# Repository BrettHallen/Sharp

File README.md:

# Sharp Projects
Projects for Sharp computers.<br>

So far:
- Sharp MZ-80B
- Sharp PC-1350
- Sharp PC-2500

## [Sharp MZ-80B](/Sharp_MZ-80B)
Currently still under its own repository but I'll move it here at some stage.

## [Sharp PC-1350](/Sharp_PC-1350)
The Sharp PC-1350 is the smaller sibling of the PC-2500.  It has the same screen resolution and BASIC but doesn't have the built-in phone book and business programs ... nor the plotter and cassette interface (these require a dock like the CE-125).

## [Sharp PC-2500](/Sharp_PC-2500)
The Sharp PC-2500 (export) and PC-2500S (domestic Japanese) were a development of the PC-1350 Pocket Computer in an A4-form factor with a full-size QWERTY keyboard and built-in 4-colour/pen plotter/printer.

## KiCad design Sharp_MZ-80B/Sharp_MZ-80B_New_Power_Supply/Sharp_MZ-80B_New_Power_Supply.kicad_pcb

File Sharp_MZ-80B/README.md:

# Sharp MZ-80B
My little repository of information about Sharp's MZ-80B all-in-one business computer from 1981.<br>

The MZ-80B is an evolution of the MZ-80K.<br>

WORK IN PROGRESS.<br>

NOTE! Any PCB designs are untested unless stated otherwise.  I have done my best to recreate them based on the schematics in the Service Manual.  (15/Feb/2026)<br>

## Videos
- [Part 1: Initial look & disassembly](https://youtu.be/cHQdRs1u79s)
- [Part 2: Keyboard refurbishment starts](https://youtu.be/vS2Di7rVlAI)
- [Part 3: Power Supply](https://youtu.be/JZkt_DzX6Ko)
- [Part 4: Monitor & Tape Deck](https://youtu.be/Ke3hOiWCVKM)
- [Part 5: New power supply](https://youtu.be/C5JBbC6FNag)
- [Part 6: It kinda works](https://youtu.be/guZFLZZtFYg)

## Specs
- Z80 at 4MHz (LH0080A)
- Power: ±5V, +12V
- 32KB RAM, expandable to 64KB
- 2KB ROM (Initial Program Loader, IPL)
- 2KB Character Generator ROM
- 2KB Character RAM
- 8KB Graphics RAM, expandable to 16KB (MZ-80GMK)

## [Components](/Sharp_MZ-80B/Components)
- IC2: Sharp X0240PA (Gate Array 14297)
- IC3: Sharp LH0080A (Z80 CPU)
- IC8: Sharp IX0285PA (IPL Boot ROM, 334-5700)
- IC19: 8253 PIT (Progammable Interval Timer)
- IC23: NEC D8255AC-5 PPI (Programmable Peripheral Interface)
- IC24: Sharp LH0081A (Z80 PIO)
- IC41: Toshiba TMM2016P-1 (2KB S-RAM)
- IC42: Sharp X0241PA (Gate Array 14298)
- IC43: Sharp X0242PA (Gate Array 14299)
- IC44: Sharp IX0286PA (CG-ROM, 334P-5701)
- DRAM: Sharp LH4116-3 (16k x 1-bit)

## [Manuals](/Sharp_MZ-80B/Manuals)
- MZ-80B Service Manual
- MZ-80B Owners Manual
- MZ-80 Monitor Reference Manual (SB-1520)

## [ROMs](/Sharp_MZ-80B/ROMs)
- 2KB Initial Program Loader (IPL)
- 2KB Character Generator
- 2KB RAM CHECK re-creation (needs testing)

## [32KB RAM Expansion](/Sharp_MZ-80B/Sharp_MZ-80B_RAM_III_IV_Expansion)
Internal expansion board to increase the RAM from 32KB to 64KB.  This design is from the Service Manual and so currently uses 4116 RAM chips.<br>

## [Base 8KB Graphics RAM (MZ-80GM)](/Sharp_MZ-80B/Sharp_MZ-80GM)
Reproduction of the base graphics RAM card (a.k.a. "GRAPHYICS-1") in the Sharp MZ-80B based on the service manual schematics.  I've updated it by replacing the original four 2KB 2016 SRAM chips with a single 32KB 62256.  Overkill, yes, but the 62256 is still available new - it reduces the chip count by four.<br>

## [8KB Graphics RAM Expansion (MZ-80GMK)](/Sharp_MZ-80B/Sharp_MZ-80GMK)
Expansion board (a.k.a. "GRAPHYICS-2") that connects to the internal Expansion Port (MZ-80EU) that doubles the graphics video RAM from 8KB to 16KB.  This design is from the Service Manual but uses a 32KB 62256 as these are still available new, rather than an obsolete 8KB 6264 or four 2KB 2016.<br>

## [DRAM to SRAM](/Sharp_MZ-80B/Sharp_MZ-80B_DRAM-to-SRAM)
Idea to replace the 16 x 4116 DRAMs of the original 32KB RAM plus the additional 16 x 4116 DRAMs of the expansion RAM with two 62256 SRAMs.<br>

## [Keyboard](/Sharp_MZ-80B/Keyboard)
Schematic and replacement PCB design.<br>

## [SD Card Interface](https://github.com/yanataka60/MZ-2000_SD)
Design (not mine!) to add SD card interface for the MZ-80B (and others).  It will work in an 80B with or without the Expansion Unit installed, which is neat.

## [Combo Graphics RAM + SD Interface](/Sharp_MZ-80B/Sharp_MZ-80GMSD)
As my MZ-80B doesn't have an expansion unit I thought about trying to add the 8KB Graphics RAM expansion (MZ-80GMK) aka "GRAPHYCS-2" on the same board as the SD interface above.  The SD board itself is still external, but the connection to the MZ-80B motherboard is included with the graphics RAM expansion.

## Power 
My 80B came from Japan so expects 100VAC and not the 240VAC we use in Australia.

### DC Requirements
| Voltage          | Current | Use                                |
|------------------|---------|------------------------------------|
| +5V regulated    | 2.5A    | motherboard & tape deck            |
| -5V regulated    | 10mA    | DRAM                               |
| +12V regulated   | 1.25A   | monitor & tape deck                |
| +12V unregulated |         | 9.5V-16.5V for tape deck solenoids |

### Connectors
Thanks to [Brad](https://www.youtube.com/@zbradbell) for figuring out they are TJC1-type.<br>

| Sharp ID      | TJC Type     | Use                                         |
|---------------|--------------|---------------------------------------------|
| QPLGN0303CEZZ | TJC1-3A      | 3-pin terminal for tape deck power on PSU   |
| DSOCN0083PAZZ | TJC1-3Y      | 3-pin socket & wires from tape deck to PSU  |
| QPLGN0103CEZZ | TJC1-1A      | 1-pin terminal for monitor power on PSU     |
| DSOCN0083PAZZ | TJC1-1Y      | 1-pin socket & wire from monitor to PSU     |
| DSOCN0098PAZZ | TJC1-4Y      | 4-pin socket & wire from PSU to motherboard |
| QPLGN0403CEZZ | TJC1-4A      | 4-pin terminal on motherboard               |
| QPLGN0303CEZZ | TJC1-3A      | 3-pin terminal for Expansion Unit power     |
|               | TJC1-T       | Contact type for sockets                    |

- [QPLGN0303CEZZ](/Sharp_MZ-80B/Images/Sharp_MZ-80B_QPLGN0303CEZZ_1.jpg)
- [DSOCN0098PAZZ](/Sharp_MZ-80B/Images/Sharp_MZ-80B_DSOCN0098PAZZ_1.png)

### New DC Power Supply
To solve my 240VAC-to-100VAC problem I thought about using a DC power supply input and then lazily using modern DC-DC switching regulators.  The main issue I can see is that the original design uses an unregulated +12VDC to power the tape eject solenoid.  This is picked up from the rectified transformer output before the +12VDC regulator which powers the monitor & tape.<br>

The tape solenoid expects a voltage between 9.5V and 16.5V.<br>

My idea was to, ahem, simply use a +15VDC input for the solenoid, and then use separate +5V, -5V and +12V regulators for the regulated supplies.  I've added some capacitors to try to soak up any voltage spikes generated by the solenoid action.<br>

Some notes:
- If I can replace the DRAM with SRAM, there is no longer a need for the -5V rail
- If I don't physically use the tape deck then there is no need for the +15V, i.e. "unregulated +12V"

## [External Audio/Video Output](/Sharp_MZ-80B/Sharp_MZ-CVBS)
A re-design of an [existing design](https://github.com/gamo256/MZ_CVBS) for replacing the CRT with an LCD, I think.  The original design uses obsolete parts (well, hard to get in Australia) so I've tried to re-design.  Let's see if it works ...<br>

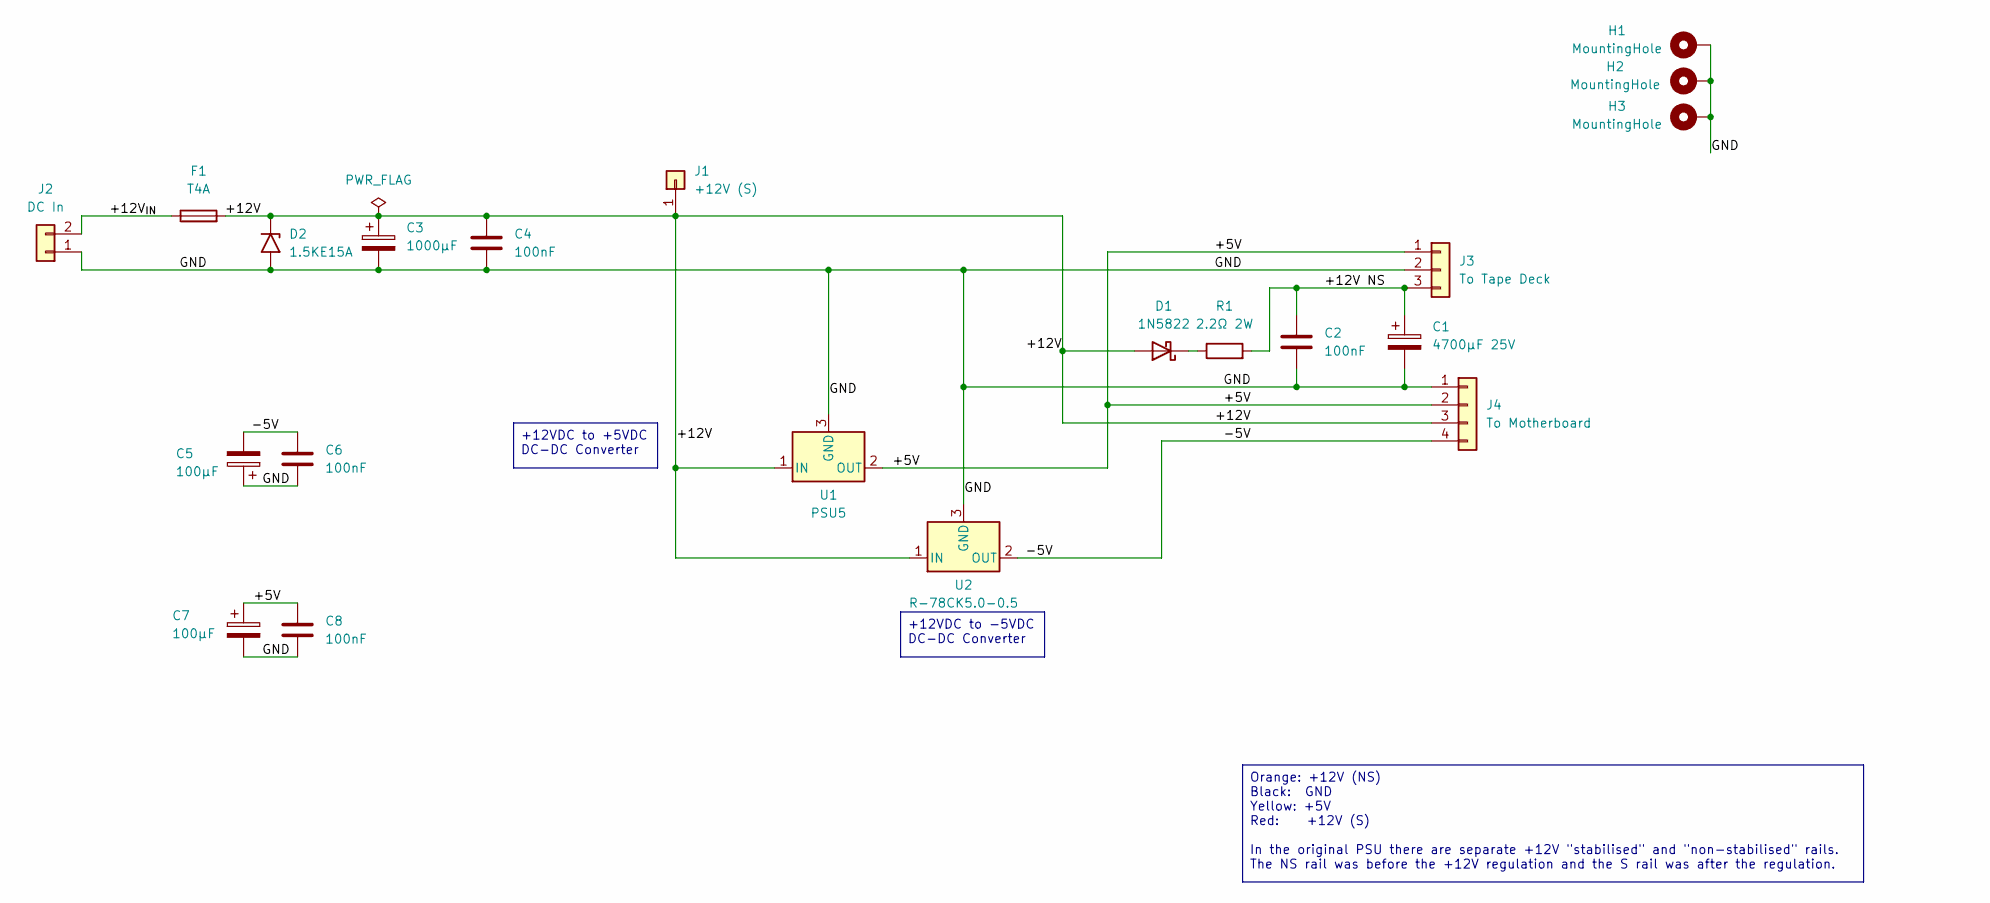
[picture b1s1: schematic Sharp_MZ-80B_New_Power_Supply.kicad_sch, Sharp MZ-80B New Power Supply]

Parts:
C1: 4700µF 25V; CP_Axial_L40.0mm_D16.0mm_P48.00mm_Horizontal
C2, C4, C6, C8: 100nF; C_Disc_D4.7mm_W2.5mm_P5.00mm
C3: 1000µF; CP_Radial_D16.0mm_P7.50mm
C5, C7: 100µF; CP_Radial_D7.5mm_P2.50mm
D1: 1N5822; D_DO-201AD_P15.24mm_Horizontal
D2: 1.5KE15A; D_DO-201AE_P15.24mm_Horizontal
F1: T4A; Littelfuse_5x20mm
H1, H2, H3: MountingHole; MountingHole_3.2mm_M3_DIN965_Pad_TopBottom
J1: +12V (S); TJC1-1A
J2: DC In; TJC1-2A
J3: To Tape Deck; TJC1-3A
J4: To Motherboard; TJC1-4A
R1: 2.2Ω 2W; R_Axial_DIN0414_L11.9mm_D4.5mm_P15.24mm_Horizontal
U1: PSU5; TO-3
U2: R-78CK5.0-0.5; TO-220-3_Vertical

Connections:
/+5V: C7.1, C8.1, J3.1, J4.2, U1.2 (OUT)
/+12V: C3.1, C4.1, D1.2 (A), D2.1 (A1), F1.2, J1.1 (Pin_1_1), J4.3, U1.1 (IN), U2.1 (IN)
/+12V NS: C1.1, C2.1, J3.3, R1.2
/+12V_{IN}: F1.1, J2.2
/-5V: C5.2, C6.1, J4.4, U2.2 (OUT)
/GND: C1.2, C2.2, C3.2, C4.2, C5.1, C6.2, C7.2, C8.2, D2.2 (A2), H1.1 (1_1), H2.1 (1_1), H3.1 (1_1), J2.1, J3.2, J4.1, U1.3 (GND), U2.3 (GND)
unnamed: D1.1 (K), R1.1

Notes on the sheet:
+12VDC to +5VDC DC-DC Converter
+12VDC to -5VDC DC-DC Converter
Orange: +12V (NS) Black: GND Yellow: +5V Red: +12V (S) In the original PSU there are separate +12V "stabilised" and "non-stabilised" rails. The NS rail was before the +12V regulation and the S rail was after the regulation.

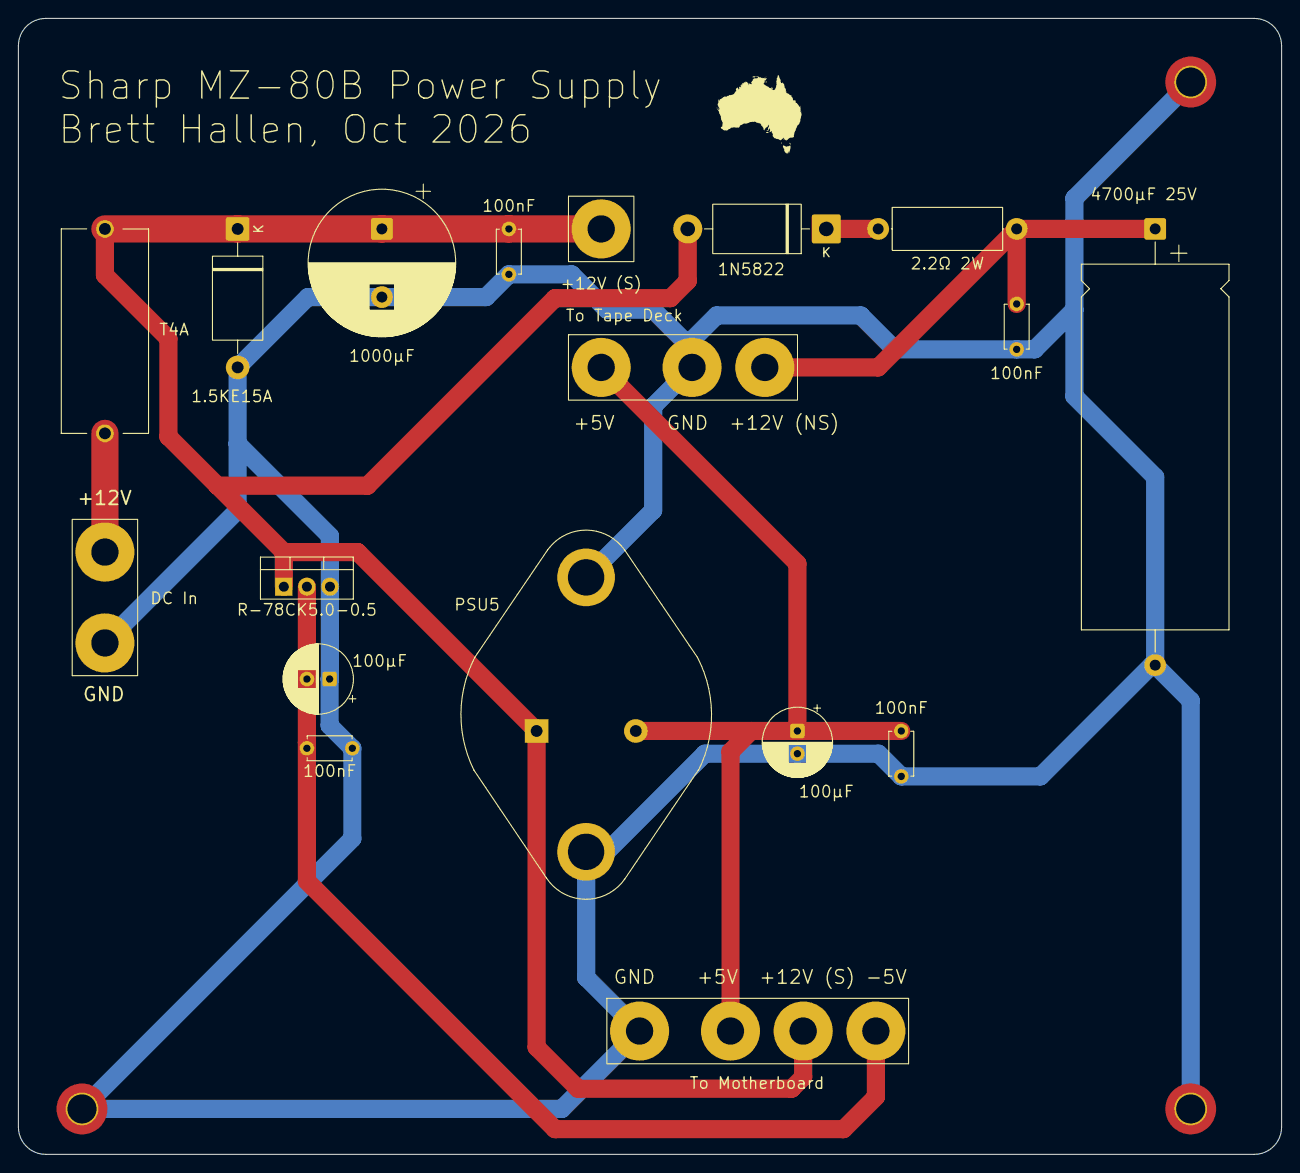
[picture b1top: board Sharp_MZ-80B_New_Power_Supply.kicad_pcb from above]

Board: 2 copper layers, 139.0 x 125.0 mm, 21 parts (0 on the bottom side), 7 nets.

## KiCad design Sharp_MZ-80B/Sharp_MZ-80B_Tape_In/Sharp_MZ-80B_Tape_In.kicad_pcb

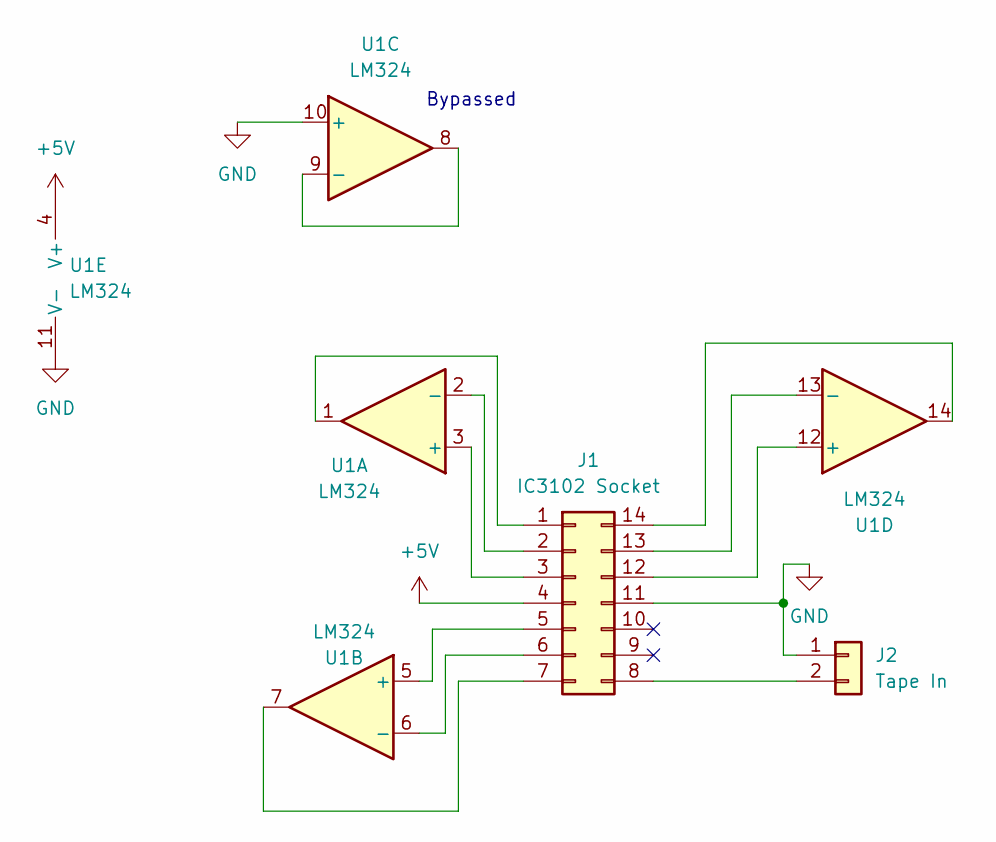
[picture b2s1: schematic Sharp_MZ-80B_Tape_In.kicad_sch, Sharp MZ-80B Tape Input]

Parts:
J1: IC3102 Socket; DIP-14_W7.62mm
J2: Tape In; PinHeader_1x02_P2.54mm_Vertical
U1: LM324; DIP-14_W7.62mm

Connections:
+5V: J1.4, U1.4 (V+)
GND: J1.11, J2.1, U1.10 (+), U1.11 (V-)
unnamed: J1.1, U1.1
unnamed: J1.2, U1.2 (-)
unnamed: J1.3, U1.3 (+)
unnamed: J1.5, U1.5 (+)
unnamed: J1.6, U1.6 (-)
unnamed: J1.7, U1.7
unnamed: J1.8, J2.2
unnamed: J1.12, U1.12 (+)
unnamed: J1.13, U1.13 (-)
unnamed: J1.14, U1.14
unnamed: U1.8, U1.9 (-)

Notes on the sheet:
Bypassed

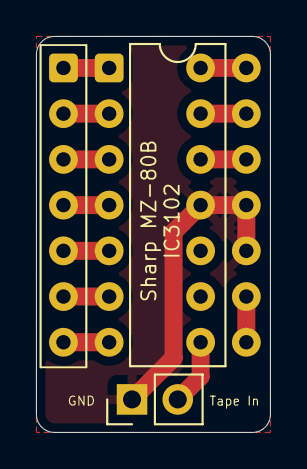
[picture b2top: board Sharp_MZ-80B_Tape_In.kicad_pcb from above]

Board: 2 copper layers, 13.0 x 22.0 mm, 3 parts (0 on the bottom side), 13 nets.

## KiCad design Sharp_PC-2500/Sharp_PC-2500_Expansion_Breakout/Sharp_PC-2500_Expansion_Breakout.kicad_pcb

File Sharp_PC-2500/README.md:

# Sharp PC-2500
The Sharp PC-2500 was a development of the Sharp PC-1350.  There were two models:<br>
- PC-2500 (export version)
- PC-2500S (domestic Japanese version)

It's an A4 format Portable Computer ... or Electronic Calculator depending on which side of the case you look at ... that runs S-BASIC and has built-in business applications.  <br>

Its 150x32 pixel LCD is capable of 24x4 characters.<br>

It uses an Hitachi SC61860 8-bit CPU with an internal 8KB ROM (code A14) for BIOS.  The S-BASIC and business applications are provided on an additional two 32KB ROMs giving 72KB of ROM in total.<br>

The other main chips are:
- SC61J216F (gate array)
- DLG3001E (PCU, printer control unit)
- SC43537 (DISP1 to DISP5)
- SC613256 (ROM1 & ROM2)
- HM6116LFP (RAM5 & RAM6)

The ROM1 code is FS43 for both models - this is S-BASIC.<br>
The ROM2 code is FS44 for Japan domestic and FS45 for export - this is for the business applications.<br>

It's quoted as having 5KB of RAM built-in but this seems inflated seeing as it only has a pair of 2KB RAM chips ... perhaps they are including the screen RAM?  The RAM can be expanded with either an 8KB or 16KB battery-backed RAM card.<br>

It includes a four pen/colour plotter/printer and has cassette and serial I/O ports.<br>

## [Manuals](/Sharp_PC-2500/Manuals)
Service manual for the PC-1350 and PC-2500.  The PC-1350 is included as it has the schematic for the CE-201 & CE-202 RAM cards.

## Videos
- [Part 1: First Look & Starting Repairs](https://youtu.be/iG-5hE-S3hM)
- [Part 2: RAM Card & Further Repairs](https://youtu.be/53tDbK7_jwQ)
- [Part 3: A working machine!](https://youtu.be/MAOv5fjzpVc)
- [Part 4: SKI JUMP Game](https://youtu.be/hhp-MKJ1q-c)

## [Internal RAM Upgrade](/Sharp_PC-2500/Sharp_PC-2500_RAM_Upgrade)
My idea to replace the RAM card interface PCB with a 16KB RAM upgrade to permanently give the machine 20KB of RAM.

## [Expansion Breakout Board](/Sharp_PC-2500/Sharp_PC-2500_Expansion_Breakout)
A breakout board for the RAM CARD interface.<br>

## [Programmes](/Sharp_PC-2500/Programmes)
I'm not aware of any programs available for this computer apart from CommAid.  The manual does have a section on how to convert programs for the PC-1210, PC-1245, PC-1260, PC-1350 and PC-1401.<br>

- Ski Jump (from the manual)

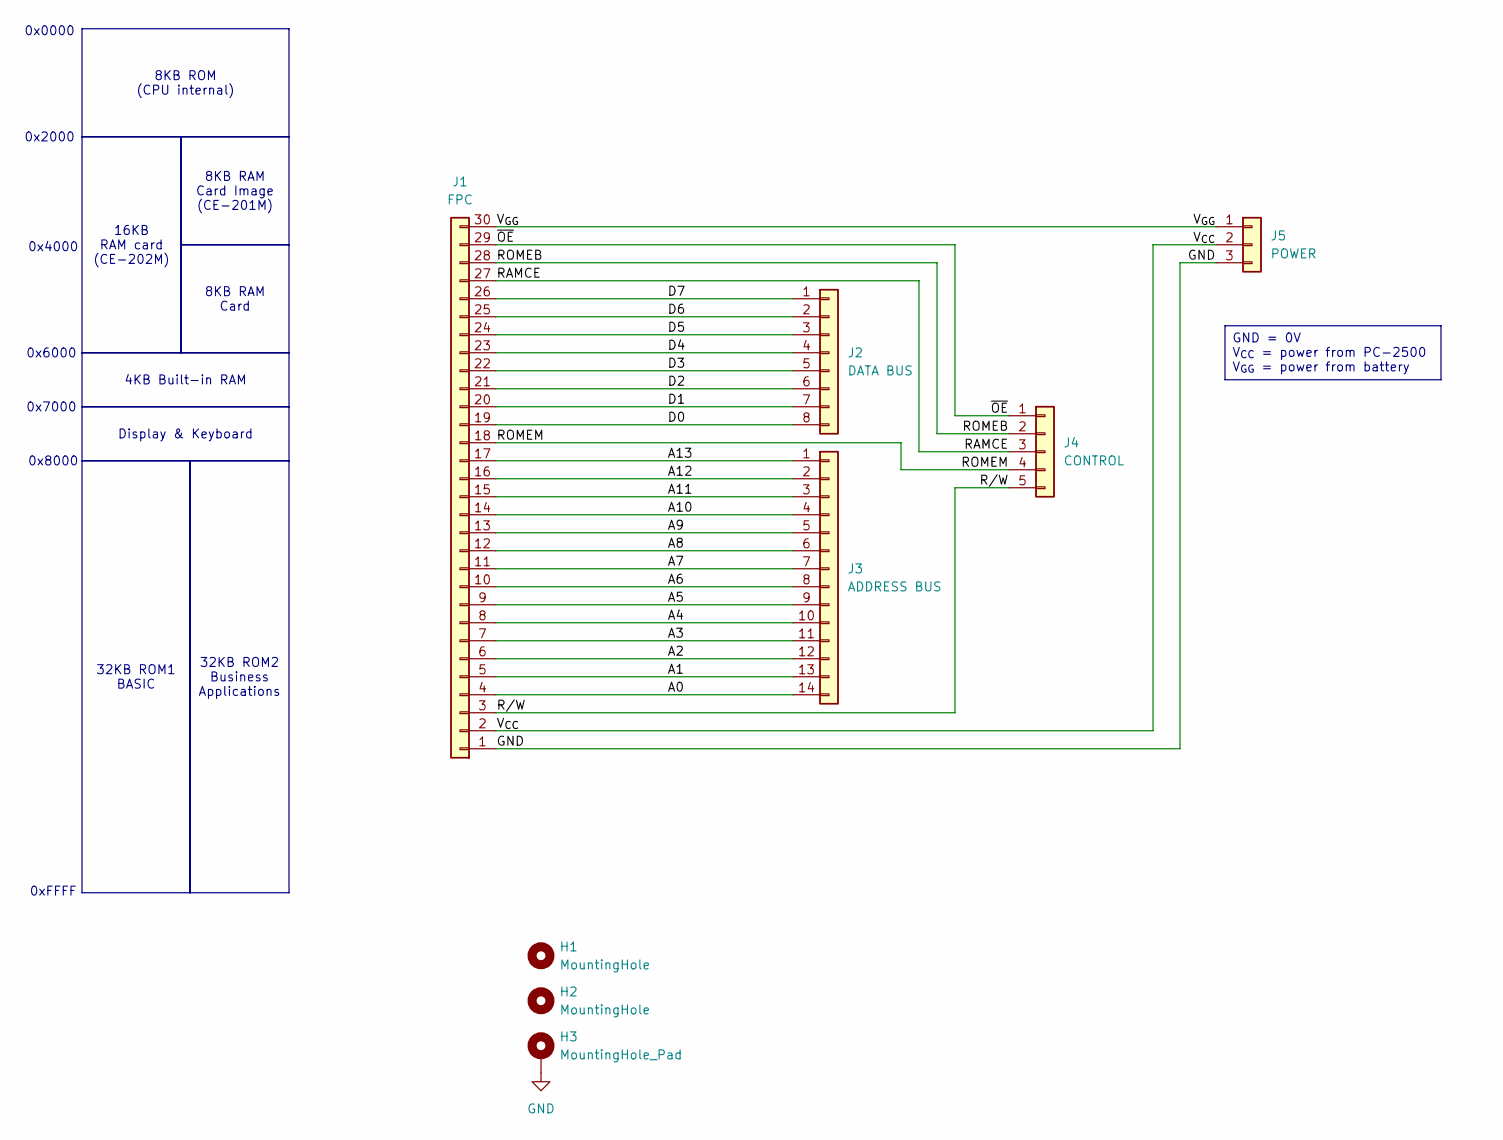
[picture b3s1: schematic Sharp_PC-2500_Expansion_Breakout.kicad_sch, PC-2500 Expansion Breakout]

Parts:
H1, H2: MountingHole; MountingHole_3.2mm_M3
H3: MountingHole_Pad; MountingHole_3.2mm_M3_DIN965_Pad_TopBottom
J1: FPC; Sharp PC-2500 30-pin TFC Connector
J2: DATA BUS; PinHeader_1x08_P2.54mm_Horizontal
J3: ADDRESS BUS; PinHeader_1x14_P2.54mm_Horizontal
J4: CONTROL; PinHeader_1x05_P2.54mm_Horizontal
J5: POWER; PinHeader_1x03_P2.54mm_Horizontal

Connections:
/A0: J1.4, J3.14
/A1: J1.5, J3.13
/A2: J1.6, J3.12
/A3: J1.7, J3.11
/A4: J1.8, J3.10
/A5: J1.9, J3.9
/A6: J1.10, J3.8
/A7: J1.11, J3.7
/A8: J1.12, J3.6
/A9: J1.13, J3.5
/A10: J1.14, J3.4
/A11: J1.15, J3.3
/A12: J1.16, J3.2
/A13: J1.17, J3.1
/D0: J1.19, J2.8
/D1: J1.20, J2.7
/D2: J1.21, J2.6
/D3: J1.22, J2.5
/D4: J1.23, J2.4
/D5: J1.24, J2.3
/D6: J1.25, J2.2
/D7: J1.26, J2.1
/RAMCE: J1.27, J4.3
/ROMEB: J1.28, J4.2
/ROMEM: J1.18, J4.4
/R/W: J1.3, J4.5
/V_{CC}: J1.2, J5.2
/V_{GG}: J1.30, J5.1
/~OE: J1.29, J4.1
GND: H3.1 (1_1), J1.1, J5.3

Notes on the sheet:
0x7000
0x8000
0x4000
0x2000
0xFFFF
0x6000
0x0000
32KB ROM2 Business Applications
Display & Keyboard
8KB RAM Card Image (CE-201M)
32KB ROM1 BASIC
16KB RAM card (CE-202M)
8KB RAM Card
8KB ROM (CPU internal)
4KB Built-in RAM
GND = 0V V_{CC} = power from PC-2500 V_{GG} = power from battery

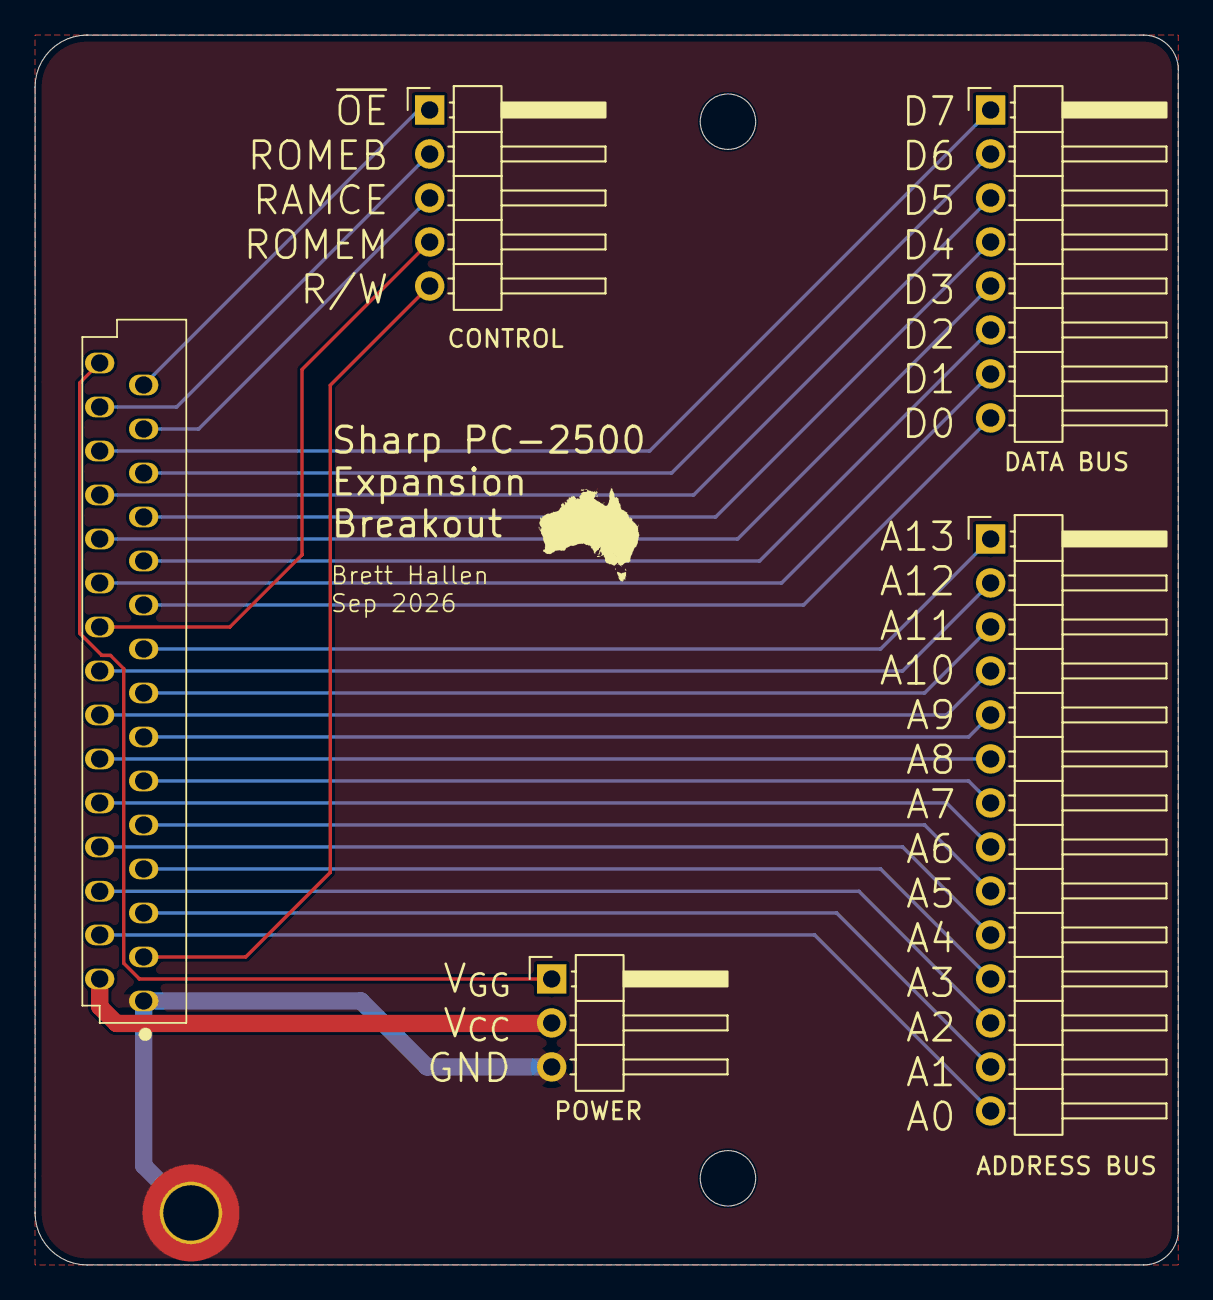
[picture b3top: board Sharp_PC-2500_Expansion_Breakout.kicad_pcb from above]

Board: 2 copper layers, 66.0 x 71.0 mm, 8 parts (0 on the bottom side), 30 nets.

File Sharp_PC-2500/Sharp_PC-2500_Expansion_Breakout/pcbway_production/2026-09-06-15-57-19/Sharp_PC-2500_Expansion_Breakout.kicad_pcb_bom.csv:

Designator,Quantity,Value,Footprint,Package,MPN,DNP,Mount_Type,Description,KiLib_Generator
J1,1,FPC,Sharp PC-2500 30-pin TFC Connector,,,,tht,"Generic connector, single row, 01x30, script generated (kicad-library-utils/schlib/autogen/connector/)",
J2,1,DATA BUS,PinHeader_1x08_P2.54mm_Horizontal,,,,tht,"Generic connector, single row, 01x08, script generated (kicad-library-utils/schlib/autogen/connector/)",connector/pin_header_socket
J3,1,ADDRESS BUS,PinHeader_1x14_P2.54mm_Horizontal,,,,tht,"Generic connector, single row, 01x14, script generated (kicad-library-utils/schlib/autogen/connector/)",connector/pin_header_socket
J4,1,CONTROL,PinHeader_1x05_P2.54mm_Horizontal,,,,tht,"Generic connector, single row, 01x05, script generated (kicad-library-utils/schlib/autogen/connector/)",connector/pin_header_socket
J5,1,POWER,PinHeader_1x03_P2.54mm_Horizontal,,,,tht,"Generic connector, single row, 01x03, script generated (kicad-library-utils/schlib/autogen/connector/)",connector/pin_header_socket

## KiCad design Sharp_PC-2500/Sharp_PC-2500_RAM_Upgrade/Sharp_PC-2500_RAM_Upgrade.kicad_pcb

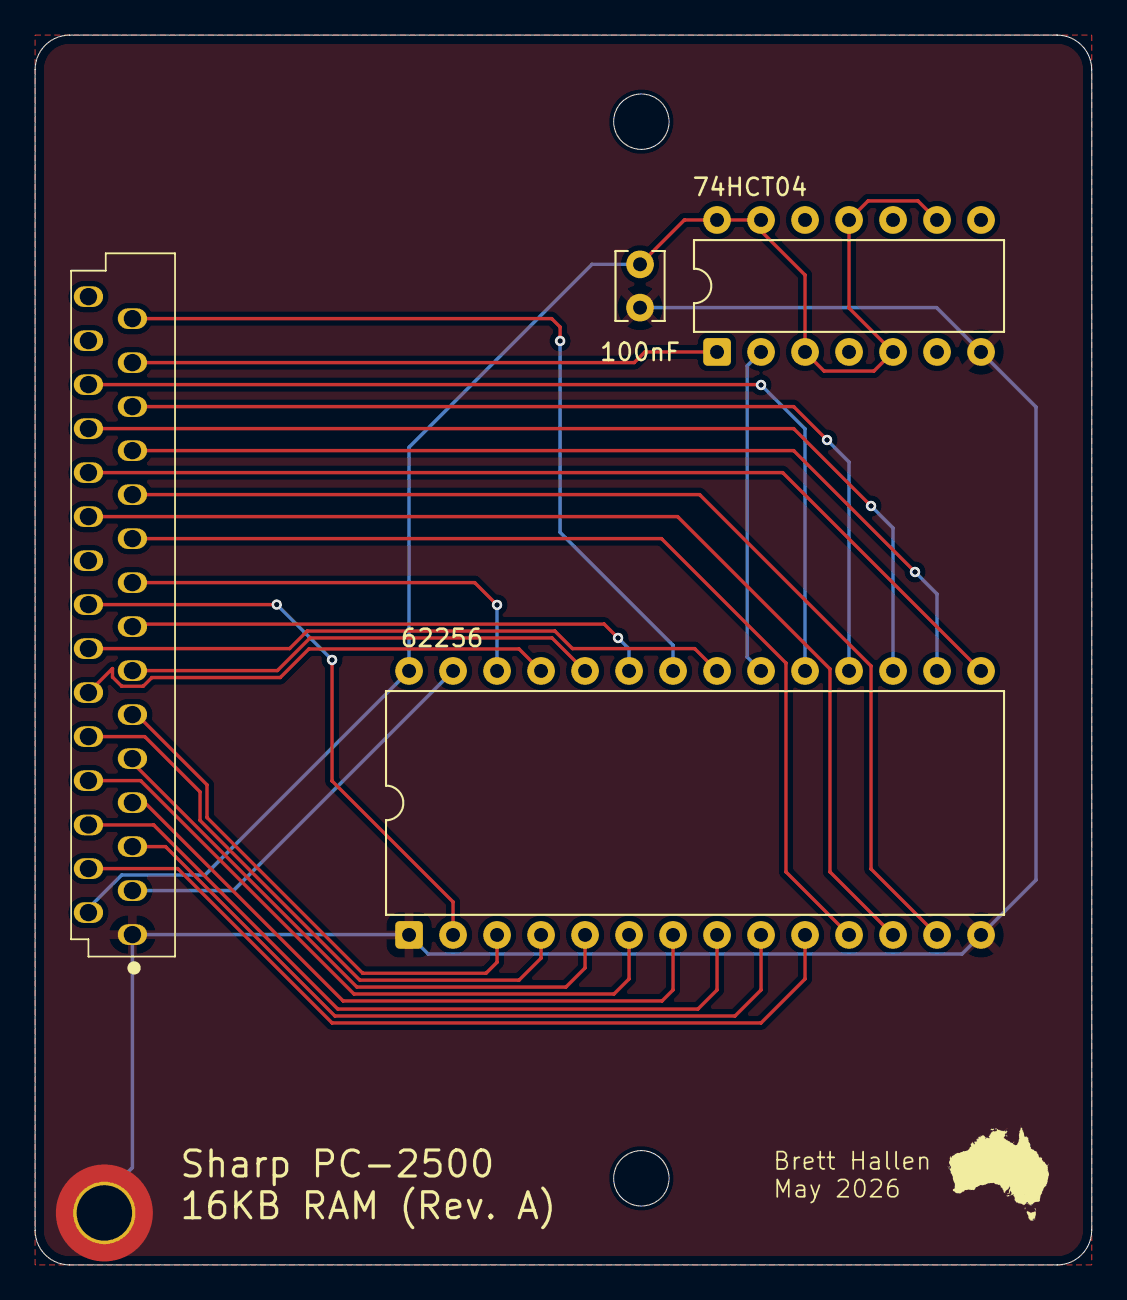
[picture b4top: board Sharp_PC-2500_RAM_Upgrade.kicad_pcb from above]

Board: 2 copper layers, 61.0 x 71.0 mm, 7 parts (0 on the bottom side), 28 nets.

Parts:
C1: 100nF; C_Disc_D3.8mm_W2.6mm_P2.50mm
H1: MountingHole_Pad; MountingHole_3.2mm_M3_DIN965_Pad_TopBottom
H2, H3: MountingHole; MountingHole_3.2mm_M3
J2: FPC; Sharp PC-2500 30-pin TFC Connector
U1: 74HCT04; DIP-14_W7.62mm
U2: 62256; DIP-28_W15.24mm

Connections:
/A0: J2.4, U2.10 (A0)
/A1: J2.5, U2.9 (A1)
/A2: J2.6, U2.8 (A2)
/A3: J2.7, U2.7 (A3)
/A4: J2.8, U2.6 (A4)
/A5: J2.9, U2.5 (A5)
/A6: J2.10, U2.4 (A6)
/A7: J2.11, U2.3 (A7)
/A8: J2.12, U2.25 (A8)
/A9: J2.13, U2.24 (A9)
/A10: J2.14, U2.21 (A10)
/A11: J2.15, U2.23 (A11)
/A12: J2.16, U2.2 (A12)
/A13: J2.17, U2.26 (A13)
/D0: J2.19, U2.11 (Q0)
/D1: J2.20, U2.12 (Q1)
/D2: J2.21, U2.13 (Q2)
/D3: J2.22, U2.15 (Q3)
/D4: J2.23, U2.16 (Q4)
/D5: J2.24, U2.17 (Q5)
/D6: J2.25, U2.18 (Q6)
/D7: J2.26, U2.19 (Q7)
/RAMCE: J2.27, U1.1
/R/W: J2.3, U2.27 (~WE)
/~OE: J2.29, U2.22 (~OE)
/~RAMCE: U1.2, U2.20 (~CS)
GND: C1.2, H1.1, J2.1, U1.7 (GND), U2.1 (A14), U2.14 (GND)
VCC: C1.1, J2.2, U1.3, U1.5, U1.9, U1.11, U1.13, U1.14 (VCC), U2.28 (VCC)

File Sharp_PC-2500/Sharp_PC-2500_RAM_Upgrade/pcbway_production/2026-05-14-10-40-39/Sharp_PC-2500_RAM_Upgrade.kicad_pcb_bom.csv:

Designator,Quantity,Value,Footprint,Package,MPN,DNP,Mount_Type,Description
C1,1,100nF,C_Disc_D3.8mm_W2.6mm_P2.50mm,,,,tht,Unpolarized capacitor
J2,1,FPC,Sharp PC-2500 30-pin TFC Connector,,,,tht,"Generic connector, single row, 01x30, script generated (kicad-library-utils/schlib/autogen/connector/)"
U1,1,74HCT04,DIP-14_W7.62mm,,,,tht,Hex Inverter
U2,1,62256,DIP-28_W15.24mm,,,,tht,"32,768-word × 8-bit High Speed CMOS Static RAM, 70ns, DIP-28"

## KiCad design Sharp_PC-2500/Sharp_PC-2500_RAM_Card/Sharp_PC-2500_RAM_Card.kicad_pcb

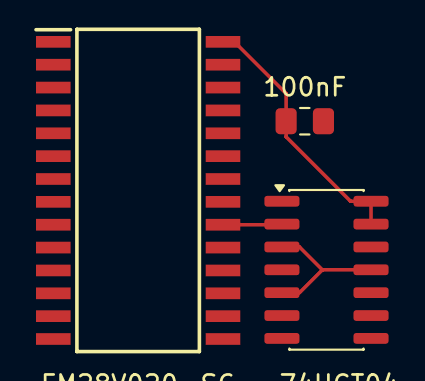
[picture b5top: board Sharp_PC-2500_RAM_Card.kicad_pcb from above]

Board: 2 copper layers, 3 parts (0 on the bottom side), 3 nets.

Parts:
C1: 100nF; C_0805_2012Metric_Pad1.18x1.45mm_HandSolder
U1: 74HCT04; SOIC-14_3.9x8.7mm_P1.27mm
U2: FM28V020-SG

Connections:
/~RAMCE: U1.2, U2.20 (~CE)
GND: C1.2, U1.7 (GND), U2.14 (VSS)
VCC: C1.1, U1.3, U1.5, U1.9, U1.11, U1.13, U1.14 (VCC), U2.1 (A14), U2.28 (VDD)

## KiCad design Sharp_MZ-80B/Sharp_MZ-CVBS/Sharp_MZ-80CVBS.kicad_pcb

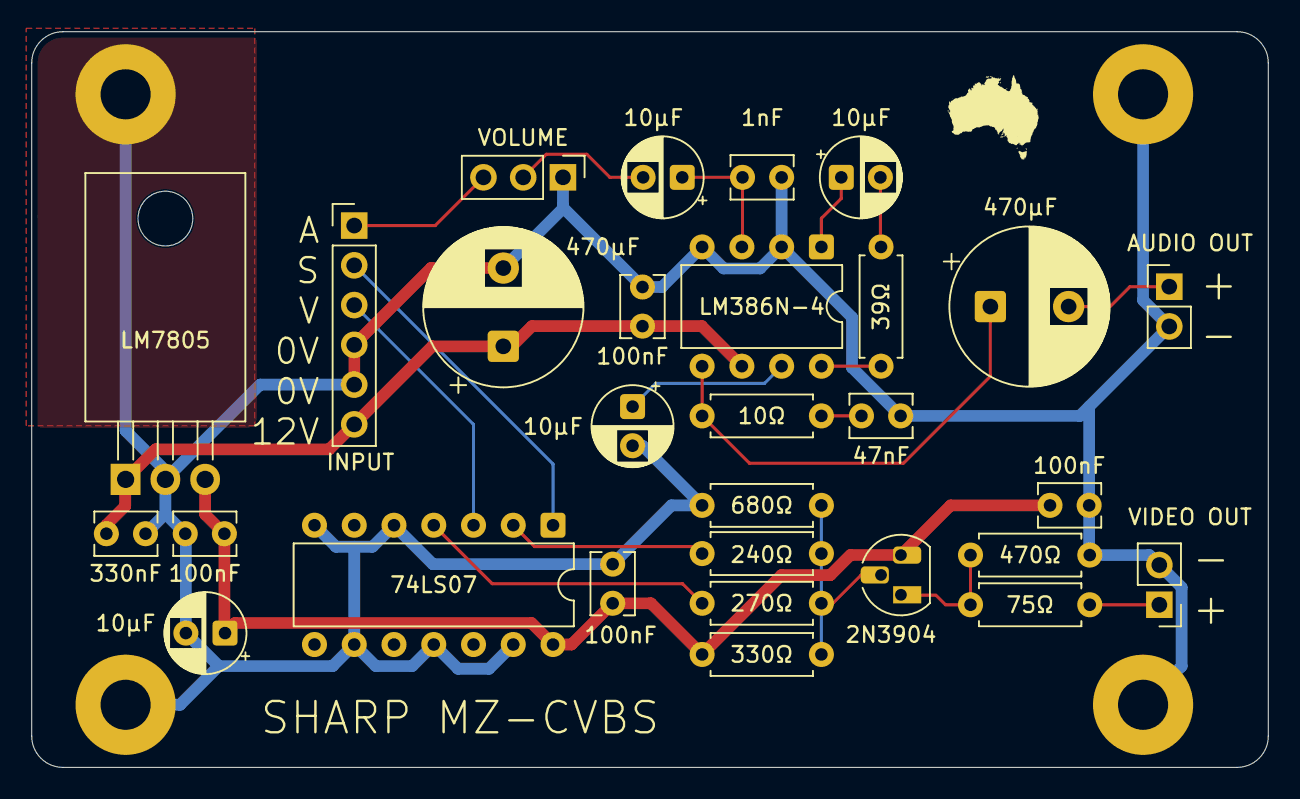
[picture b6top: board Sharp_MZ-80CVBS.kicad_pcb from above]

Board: 2 copper layers, 79.0 x 47.0 mm, 33 parts (0 on the bottom side), 20 nets.

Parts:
C1, C5: 470µF; CP_Radial_D10.0mm_P5.00mm
C2, C4, C8, C11: 10µF; CP_Radial_D5.0mm_P2.50mm
C3, C9, C12, C13: 100nF; C_Disc_D3.8mm_W2.6mm_P2.50mm
C6: 1nF; C_Disc_D3.8mm_W2.6mm_P2.50mm
C7: 47nF; C_Disc_D3.8mm_W2.6mm_P2.50mm
C10: 330nF; C_Disc_D3.8mm_W2.6mm_P2.50mm
H1, H2, H3, H4: MountingHole_Pad; MountingHole_3.2mm_M3_Pad
J1: VOLUME; PinHeader_1x03_P2.54mm_Vertical
J2: AUDIO OUT; PinHeader_1x02_P2.54mm_Vertical
J3: INPUT; PinHeader_1x06_P2.54mm_Vertical
J4: VIDEO OUT; PinHeader_1x02_P2.54mm_Vertical
Q1: 2N3904; TO-92_HandSolder
R1: 10Ω; R_Axial_DIN0207_L6.3mm_D2.5mm_P7.62mm_Horizontal
R2: 39Ω; R_Axial_DIN0207_L6.3mm_D2.5mm_P7.62mm_Horizontal
R3: 240Ω; R_Axial_DIN0207_L6.3mm_D2.5mm_P7.62mm_Horizontal
R4: 330Ω; R_Axial_DIN0207_L6.3mm_D2.5mm_P7.62mm_Horizontal
R5: 75Ω; R_Axial_DIN0207_L6.3mm_D2.5mm_P7.62mm_Horizontal
R6: 270Ω; R_Axial_DIN0207_L6.3mm_D2.5mm_P7.62mm_Horizontal
R7: 680Ω; R_Axial_DIN0207_L6.3mm_D2.5mm_P7.62mm_Horizontal
R8: 470Ω; R_Axial_DIN0207_L6.3mm_D2.5mm_P7.62mm_Horizontal
U1: 74LS07; DIP-14_W7.62mm
U2: LM386N-4; DIP-8_W7.62mm
U3: LM7805; TO-220-3_Horizontal_TabDown

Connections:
+5V: C9.1, C11.1, C12.1, C13.1, Q1.3 (C), R4.1, U1.14 (VCC), U3.3 (VO)
+12V: C1.1, C3.1, C10.1, J3.6, U2.6 (V+), U3.1 (VI)
/AUDIO: J1.3, J3.1
/SYNC: J3.2, U1.1
/VIDEO: J3.3, U1.3
GND: C1.2, C2.2, C3.2, C6.2, C7.2, C9.2, C10.2, C11.2, C12.2, C13.2, H1.1 (1_1), H2.1 (1_1), H3.1 (1_1), H4.1 (1_1), J1.1, J2.2, J3.4, J3.5, J4.2, R7.1, R8.1, U1.5, U1.7 (GND), U1.9, U1.11, U1.13, U2.2 (-), U2.4 (GND), U3.2 (GND)
unnamed: C5.1, R1.1, U2.5
unnamed: C7.1, R1.2
unnamed: C8.1, U2.1 (GAIN)
unnamed: C8.2, R2.2
unnamed: C4.2, J1.2
unnamed: C5.2, J2.1
unnamed: J4.1, R5.2
unnamed: Q1.2 (B), R3.2, R4.2, R6.2, R7.2
unnamed: Q1.1 (E), R5.1, R8.2
unnamed: R2.1, U2.8 (GAIN)
unnamed: R3.1, U1.2
unnamed: R6.1, U1.4
unnamed: C4.1, C6.1, U2.3 (+)
unnamed: C2.1, U2.7 (BYPASS)

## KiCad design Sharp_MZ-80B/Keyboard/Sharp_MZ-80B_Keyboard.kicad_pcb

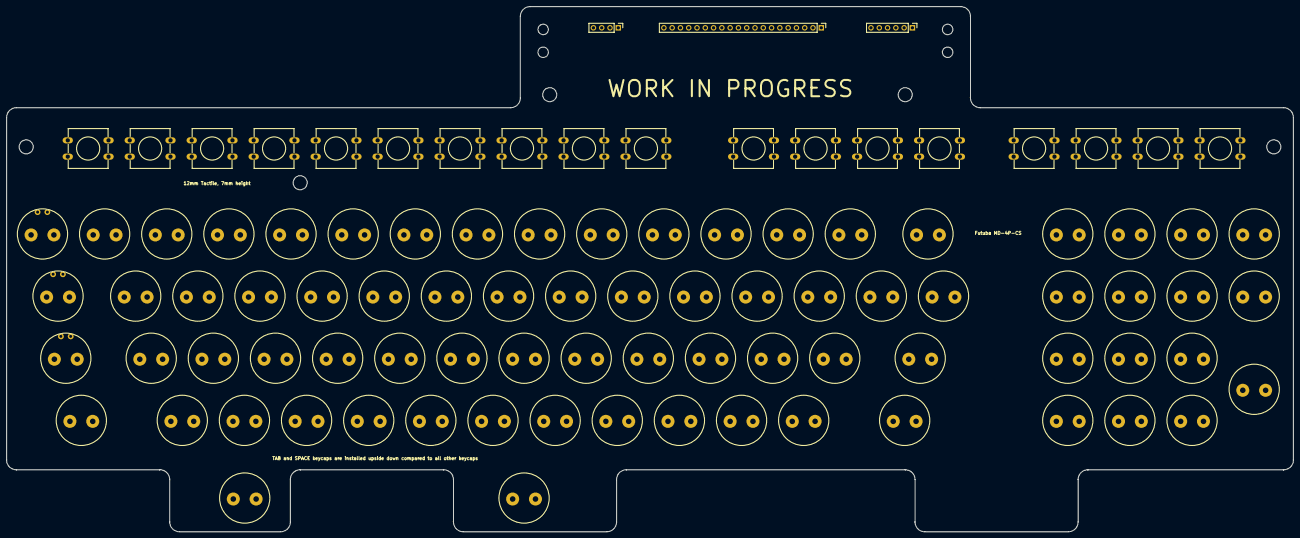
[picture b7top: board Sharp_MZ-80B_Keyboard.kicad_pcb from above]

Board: 2 copper layers, 394.5 x 161.0 mm, 104 parts (0 on the bottom side), 29 nets, no tracks yet.

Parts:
H1, H2, H3, H4, H5: MountingHole; MountingHole_4.3mm_M4
H6, H7, H8, H9: MountingHole; MountingHole_3.2mm_M3
J1: Tape Controls; PinHeader_1x06_P2.54mm_Vertical
J2: Keyboard Matrix; PinHeader_1x20_P2.54mm_Vertical
J3: LEDs; PinHeader_1x04_P2.54mm_Vertical
SW1: CMT_EJECT; SW_PUSH-12mm
SW2: CMT_FF; SW_PUSH-12mm
SW3: CMT_REW; SW_PUSH-12mm
SW4: CMT_STOP; SW_PUSH-12mm
SW5: ]; Futuba MD-4P
SW6: CLR HOME; Futuba MD-4P
SW7: INST DEL; Futuba MD-4P
SW8: 8; Futuba MD-4P
SW9: 9; Futuba MD-4P
SW10: COLON; Futuba MD-4P
SW11: SEMI COLON; Futuba MD-4P
SW12: -; Futuba MD-4P
SW13: @; Futuba MD-4P
SW14: [; Futuba MD-4P
SW15: ZERO; Futuba MD-4P
SW16: 1; Futuba MD-4P
SW17: 2; Futuba MD-4P
SW18: 3; Futuba MD-4P
SW19: 4; Futuba MD-4P
SW20: 5; Futuba MD-4P
SW21: 6; Futuba MD-4P
SW22: 7; Futuba MD-4P
SW23: X; Futuba MD-4P
SW24: Y; Futuba MD-4P
SW25: Z; Futuba MD-4P
SW26: ^; Futuba MD-4P
SW27: \; Futuba MD-4P
SW28: ?; Futuba MD-4P
SW29: DOT; Futuba MD-4P
SW30: COMMA; Futuba MD-4P
SW31: P; Futuba MD-4P
SW32: Q; Futuba MD-4P
SW33: R; Futuba MD-4P
SW34: S; Futuba MD-4P
SW35: T; Futuba MD-4P
SW36: U; Futuba MD-4P
SW37: V; Futuba MD-4P
SW38: W; Futuba MD-4P
SW39: I; Futuba MD-4P
SW40: H; Futuba MD-4P
SW41: J; Futuba MD-4P
SW42: K; Futuba MD-4P
SW43: L; Futuba MD-4P
SW44: M; Futuba MD-4P
SW45: N; Futuba MD-4P
SW46: O; Futuba MD-4P
SW47: /; Futuba MD-4P
SW48: A; Futuba MD-4P
SW49: B; Futuba MD-4P
SW50: C; Futuba MD-4P
SW51: D; Futuba MD-4P
SW52: E; Futuba MD-4P
SW53: F; Futuba MD-4P
SW54: G; Futuba MD-4P
SW55: TAB; Futuba MD-4P
SW56: SPACE; Futuba MD-4P
SW57: CR; Futuba MD-4P
SW58: UP; SW_PUSH-12mm
SW59: DOWN; SW_PUSH-12mm
SW60: LEFT; SW_PUSH-12mm
SW61: RIGHT; SW_PUSH-12mm
SW62: BREAK; Futuba MD-4P
SW63: GRPH; Futuba MD-7
SW64: NP 0; Futuba MD-4P
SW65: NP 1; Futuba MD-4P
SW66: NP 2; Futuba MD-4P
SW67: NP 3; Futuba MD-4P
SW68: NP 4; Futuba MD-4P
SW69: NP 5; Futuba MD-4P
SW70: NP 6; Futuba MD-4P
SW71: NP 7; Futuba MD-4P
SW72: SFT LOCK; Futuba MD-7
SW73: F9; SW_PUSH-12mm
SW74: F10; SW_PUSH-12mm
SW75: NP 8; Futuba MD-4P
SW76: NP 9; Futuba MD-4P
SW77: NP 00; Futuba MD-4P
SW78: NP DOT; Futuba MD-4P
SW79: NP PLUS; Futuba MD-4P
SW80: NP MINUS; Futuba MD-4P
SW81: F1; SW_PUSH-12mm
SW82: F2; SW_PUSH-12mm
SW83: F3; SW_PUSH-12mm
SW84: F4; SW_PUSH-12mm
SW85: F5; SW_PUSH-12mm
SW86: F6; SW_PUSH-12mm
SW87: F7; SW_PUSH-12mm
SW88: F8; SW_PUSH-12mm
SW89: カナ RVS; Futuba MD-7
SW90: RH SHIFT; Futuba MD-4P
SW91: LH_SHIFT; Futuba MD-4P
SW92: NP ENT; Futuba MD-4P

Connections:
CMT_COMMON: J1.6, SW1.2, SW2.2, SW3.2
CMT_EJECT: J1.1, SW1.1
CMT_FF: J1.5, SW2.1
CMT_REW: J1.4, SW3.1
CMT_STOP1: J1.2, SW4.1
CMT_STOP2: J1.3, SW4.2
COL0: J2.1, SW5.1, SW8.1, SW15.1, SW23.1, SW31.1, SW39.1, SW47.1, SW55.1, SW63.1, SW64.1, SW73.1, SW81.1
COL1: J2.2, SW9.1, SW16.1, SW24.1, SW32.1, SW40.1, SW48.1, SW56.1, SW65.1, SW72.1, SW74.1, SW82.1
COL2: J2.3, SW6.1, SW10.1, SW17.1, SW25.1, SW33.1, SW41.1, SW49.1, SW57.1, SW66.1, SW75.1, SW83.1, SW90.1, SW91.1, SW92.1
COL3: J2.4, SW7.1, SW11.1, SW18.1, SW26.1, SW34.1, SW42.1, SW50.1, SW58.1, SW67.1, SW76.1, SW84.1, SW89.1
COL4: J2.5, SW12.1, SW19.1, SW27.1, SW35.1, SW43.1, SW51.1, SW59.1, SW68.1, SW77.1, SW85.1
COL5: J2.6, SW13.1, SW20.1, SW28.1, SW36.1, SW44.1, SW52.1, SW60.1, SW69.1, SW78.1, SW86.1
COL6: J2.7, SW14.1, SW21.1, SW29.1, SW37.1, SW45.1, SW53.1, SW61.1, SW70.1, SW79.1, SW87.1
COL7: J2.8, SW22.1, SW30.1, SW38.1, SW46.1, SW54.1, SW62.1, SW71.1, SW80.1, SW88.1
GRPH_LED: J3.3, SW63.3 (K), SW72.3 (K)
LED_COMMON: J3.1, SW63.2, SW72.2, SW89.2
ROW0: J2.9, SW63.4 (A), SW72.4 (A), SW89.4 (A), SW90.2, SW91.2
ROW1: J2.10, SW5.2, SW6.2, SW7.2
ROW2: J2.11, SW8.2, SW9.2, SW10.2, SW11.2, SW12.2, SW13.2, SW14.2
ROW3: J2.12, SW15.2, SW16.2, SW17.2, SW18.2, SW19.2, SW20.2, SW21.2, SW22.2
ROW4: J2.13, SW23.2, SW24.2, SW25.2, SW26.2, SW27.2, SW28.2, SW29.2, SW30.2
ROW5: J2.14, SW31.2, SW32.2, SW33.2, SW34.2, SW35.2, SW36.2, SW37.2, SW38.2
ROW6: J2.15, SW39.2, SW40.2, SW41.2, SW42.2, SW43.2, SW44.2, SW45.2, SW46.2
ROW7: J2.16, SW47.2, SW48.2, SW49.2, SW50.2, SW51.2, SW52.2, SW53.2, SW54.2
ROW8: J2.17, SW55.2, SW56.2, SW57.2, SW58.2, SW59.2, SW60.2, SW61.2, SW62.2, SW92.2
ROW9: J2.18, SW64.2, SW65.2, SW66.2, SW67.2, SW68.2, SW69.2, SW70.2, SW71.2
ROW10: J2.19, SW73.2, SW74.2, SW75.2, SW76.2, SW77.2, SW78.2, SW79.2, SW80.2
ROW11: J2.20, SW81.2, SW82.2, SW83.2, SW84.2, SW85.2, SW86.2, SW87.2, SW88.2
カナ_RVS_LED: J3.2, SW89.3 (K)

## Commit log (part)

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2026-05-10 Work in progress
